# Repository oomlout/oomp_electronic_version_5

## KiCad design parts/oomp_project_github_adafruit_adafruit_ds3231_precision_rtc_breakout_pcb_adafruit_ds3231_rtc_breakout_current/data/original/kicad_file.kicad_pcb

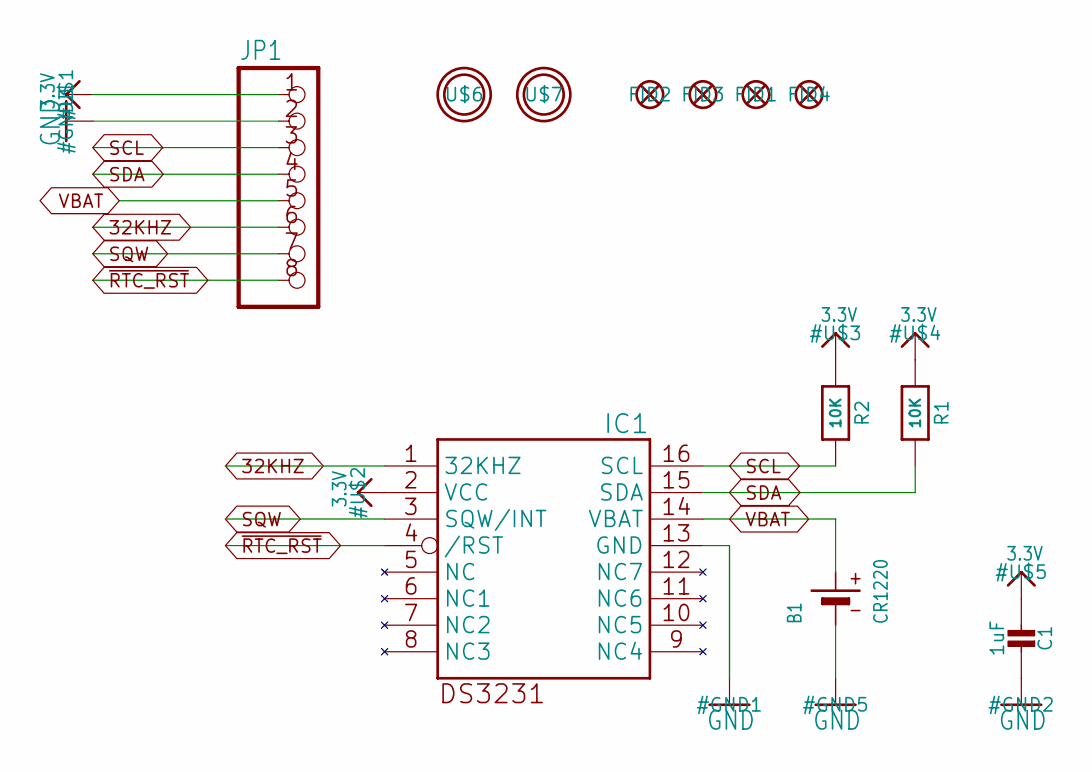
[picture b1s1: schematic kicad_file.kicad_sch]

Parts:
B1: CR1220
C1: 1uF; 0805-NO
FID1, FID2, FID3, FID4: FIDUCIAL""; FIDUCIAL_1MM
IC1: DS3231/SO; SO16W
JP1: HEADER-1X870MIL; 1X08_ROUND_70
R1, R2: 10K; 0805-NO
U$6, U$7: MOUNTINGHOLE2.5; MOUNTINGHOLE_2.5_PLATED

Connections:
3.3V: C1.2, IC1.2 (VCC), JP1.1, R1.1, R2.1
32KHZ: IC1.1 (32KHZ), JP1.6
GND: B1.-, C1.1, IC1.13 (GND), JP1.2
SCL: IC1.16 (SCL), JP1.3, R2.2
SDA: IC1.15 (SDA), JP1.4, R1.2
SQW: IC1.3 (SQW/INT), JP1.7
VBAT: B1.+$1 (+), IC1.14 (VBAT), JP1.5
~RTC_RST: IC1.4 (/RST), JP1.8

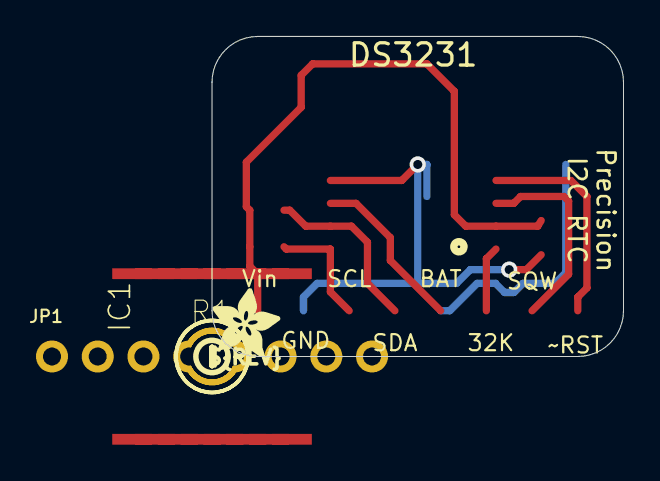
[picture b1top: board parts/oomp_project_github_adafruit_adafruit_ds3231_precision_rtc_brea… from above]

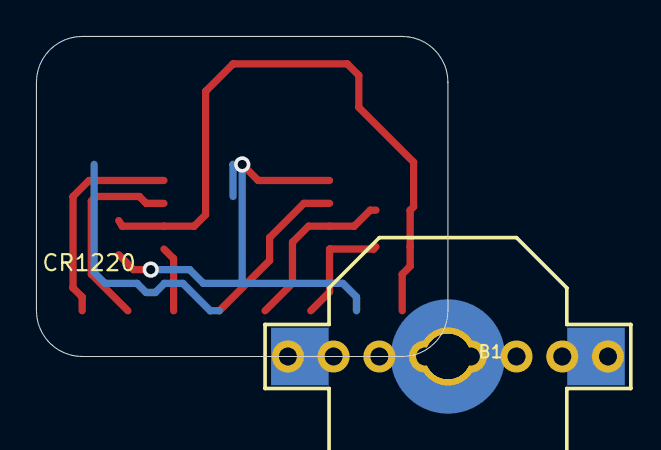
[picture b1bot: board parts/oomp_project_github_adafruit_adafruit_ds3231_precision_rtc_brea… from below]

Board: 16 copper layers, 22.9 x 17.8 mm, 14 parts (3 on the bottom side), 8 nets.

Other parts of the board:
U$8: ADAFRUIT_3.5MM
U$9: PCBFEAT-REV-040

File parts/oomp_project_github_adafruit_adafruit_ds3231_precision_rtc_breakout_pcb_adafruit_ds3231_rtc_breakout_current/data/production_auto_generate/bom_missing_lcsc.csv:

Designator,Comment,Footprint,OOMP ID,Reason
B1,CR1220,Adafruit DS3231 RTC Breakout-import-fps:CR1220,,No verified LCSC part number
C1,1uF,Adafruit DS3231 RTC Breakout-import-fps:0805-NO,,No verified LCSC part number
IC1,DS3231/SO,Adafruit DS3231 RTC Breakout-import-fps:SO16W,,No verified LCSC part number
U$8,,Adafruit DS3231 RTC Breakout-import-fps:ADAFRUIT_3.5MM,,No verified LCSC part number
U$9,,Adafruit DS3231 RTC Breakout-import-fps:PCBFEAT-REV-040,,No verified LCSC part number

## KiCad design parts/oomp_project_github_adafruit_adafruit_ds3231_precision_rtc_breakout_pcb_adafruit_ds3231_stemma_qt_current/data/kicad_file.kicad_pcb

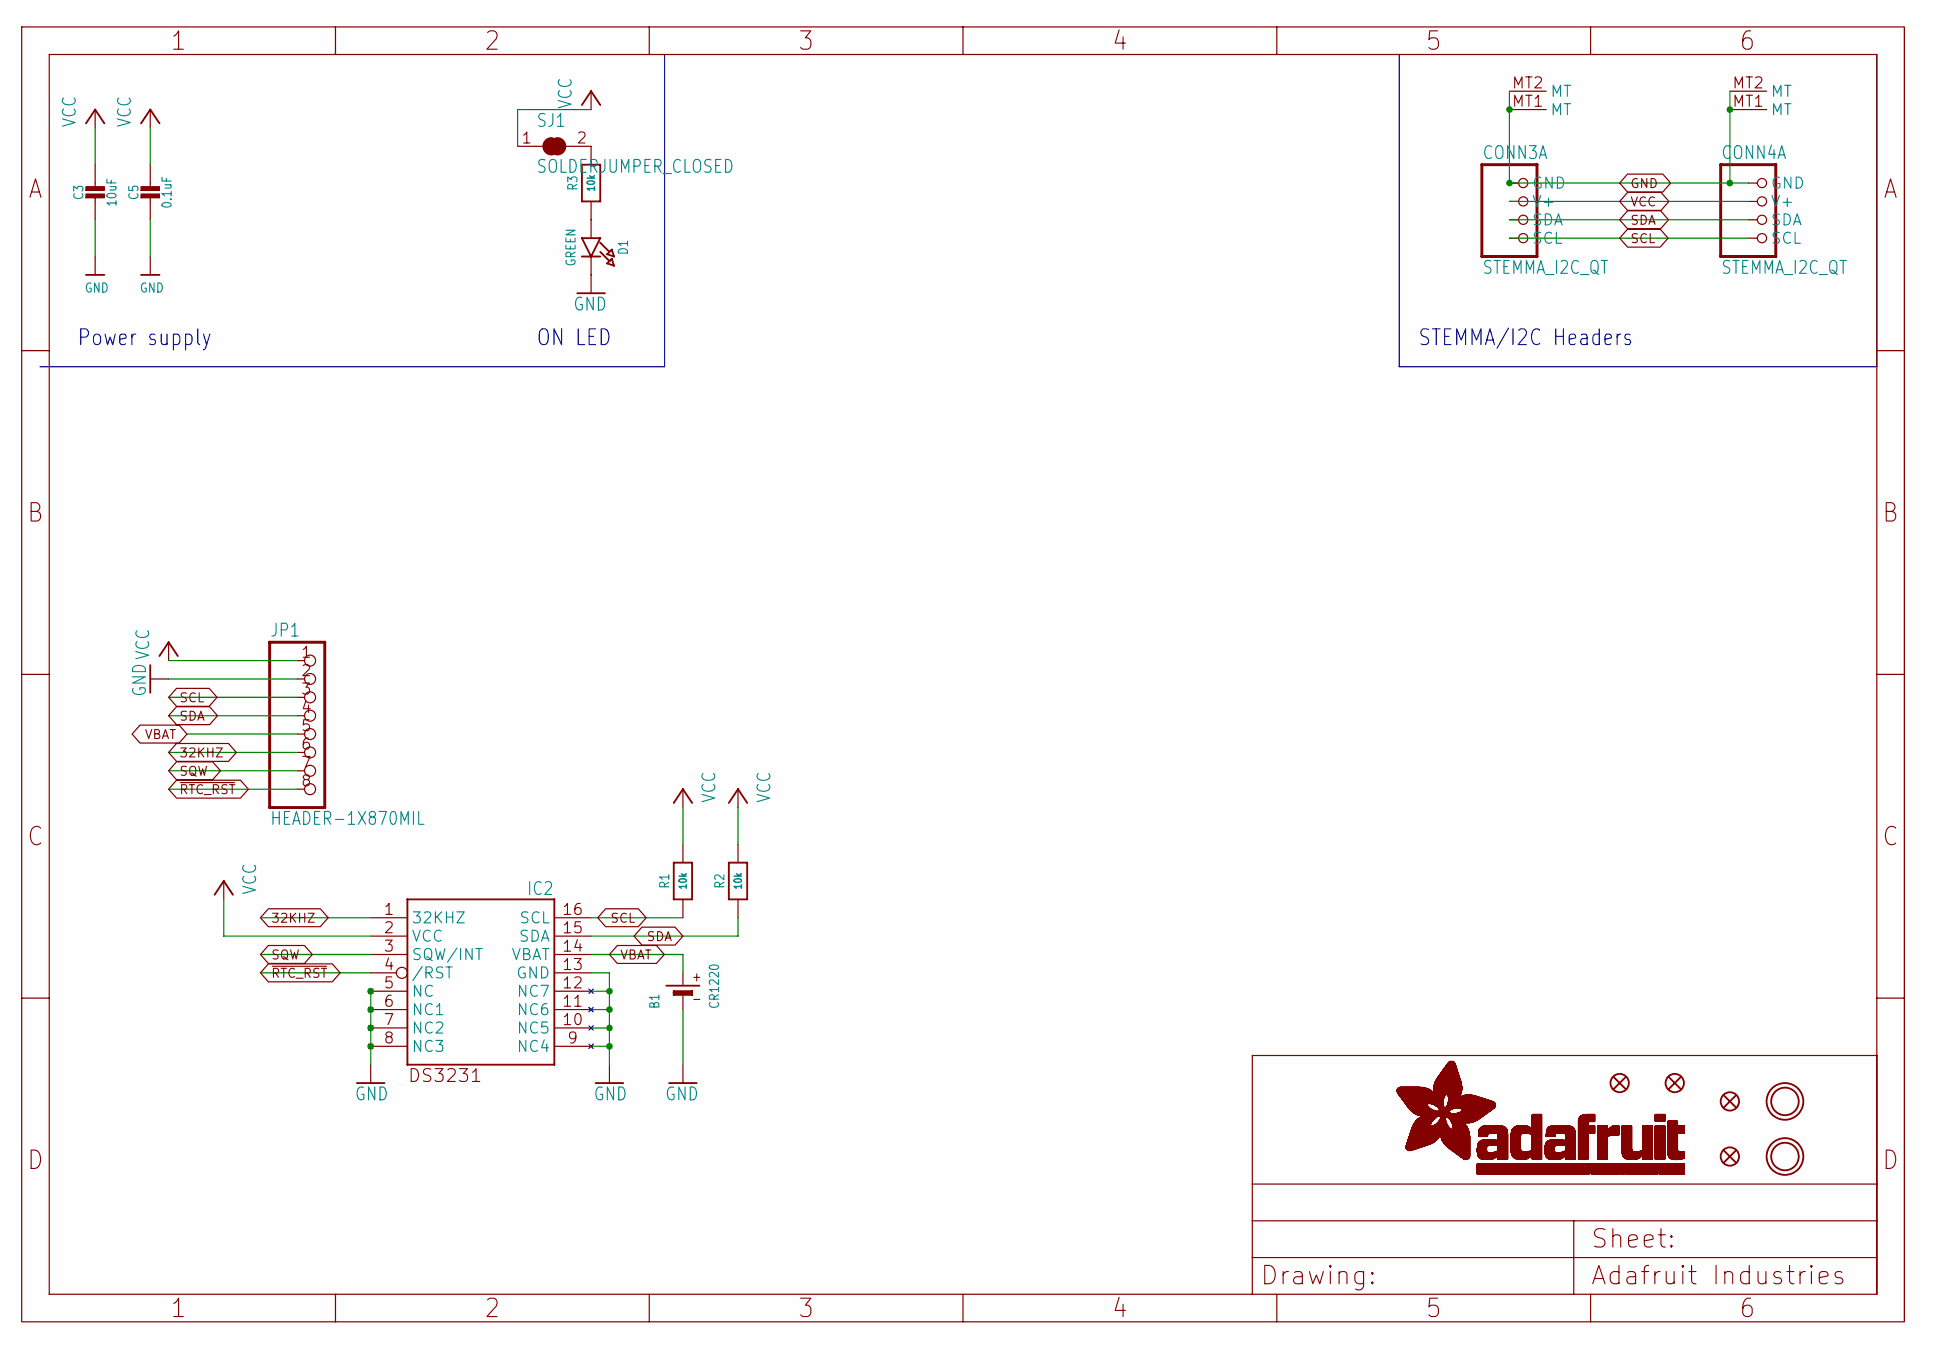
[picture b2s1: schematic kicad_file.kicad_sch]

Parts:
B1: CR1220
C3: 10uF; 0805-NO
C5: 0.1uF; 0603-NO
CONN3, CONN4: STEMMA_I2C_QT; JST_SH4
D1: GREEN; CHIPLED_0603_NOOUTLINE
FID1, FID2, FID3, FID4: FIDUCIAL_1MM
IC2: DS3231/SO; SO16W
JP1: HEADER-1X870MIL; 1X08_ROUND_70
R1, R2, R3: 10k; 0603-NO
SJ1: SOLDERJUMPER_CLOSED; SOLDERJUMPER_CLOSEDWIRE
U$9, U$17: MOUNTINGHOLE3.0THIN; MOUNTINGHOLE_3.0_PLATEDTHIN

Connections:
32KHZ: IC2.1 (32KHZ), JP1.6
GND: B1.-, C3.2, C5.2, CONN3.1 (GND), CONN3.MT1 (MT), CONN3.MT2 (MT), CONN4.1 (GND), CONN4.MT1 (MT), CONN4.MT2 (MT), D1.C, IC2.5 (NC), IC2.6 (NC1), IC2.7 (NC2), IC2.8 (NC3), IC2.9 (NC4), IC2.10 (NC5), IC2.11 (NC6), IC2.12 (NC7), IC2.13 (GND), JP1.2
unnamed: R3.2, SJ1.2
unnamed: D1.A, R3.1
SCL: CONN3.4 (SCL), CONN4.4 (SCL), IC2.16 (SCL), JP1.3, R1.1
SDA: CONN3.3 (SDA), CONN4.3 (SDA), IC2.15 (SDA), JP1.4, R2.1
SQW: IC2.3 (SQW/INT), JP1.7
VBAT: B1.+$1 (+), B1.+$2 (+), IC2.14 (VBAT), JP1.5
VCC: C3.1, C5.1, CONN3.2 (V+), CONN4.2 (V+), IC2.2 (VCC), JP1.1, R1.2, R2.2, SJ1.1
~RTC_RST: IC2.4 (/RST), JP1.8

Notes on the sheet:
Power supply
ON LED
STEMMA/I2C Headers

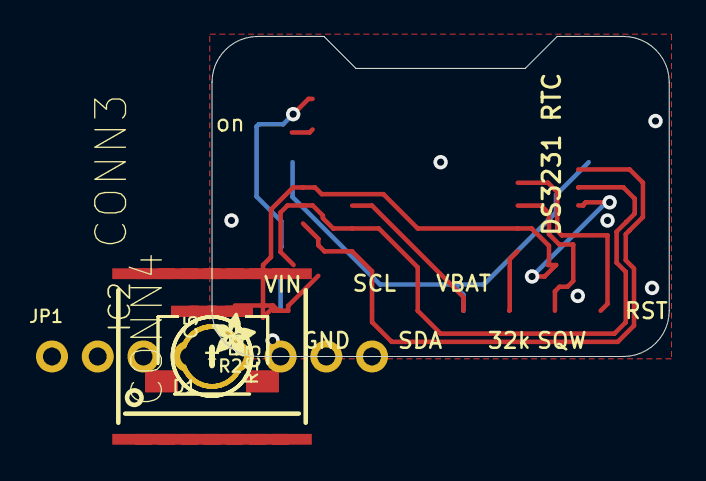
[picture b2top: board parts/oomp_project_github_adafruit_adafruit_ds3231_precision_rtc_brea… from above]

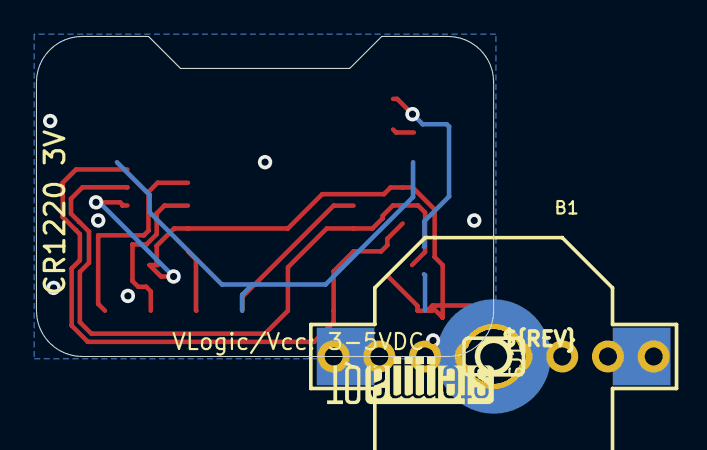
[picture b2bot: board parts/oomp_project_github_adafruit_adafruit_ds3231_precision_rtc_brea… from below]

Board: 16 copper layers, 25.4 x 17.8 mm, 21 parts (6 on the bottom side), 10 nets.

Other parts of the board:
U$1: ADAFRUIT_2.5MM
U$25: PCBFEAT-REV-040
U$31: STEMMAQT

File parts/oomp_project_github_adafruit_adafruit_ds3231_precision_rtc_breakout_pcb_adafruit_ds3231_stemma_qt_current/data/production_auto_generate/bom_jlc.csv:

Comment,Designator,Footprint,LCSC Part #
,JP1,Adafruit DS3231 STEMMA QT-import-fps:1X08_ROUND_70,C492421
,U$1,Adafruit DS3231 STEMMA QT-import-fps:ADAFRUIT_2.5MM,
,U$25,Adafruit DS3231 STEMMA QT-import-fps:PCBFEAT-REV-040,
,U$31,Adafruit DS3231 STEMMA QT-import-fps:STEMMAQT,
0.1uF,C5,Adafruit DS3231 STEMMA QT-import-fps:0603-NO,C14663
10k,"R1,R2,R3",Adafruit DS3231 STEMMA QT-import-fps:0603-NO,C98220
10uF,C3,Adafruit DS3231 STEMMA QT-import-fps:0805-NO,
CR1220,B1,Adafruit DS3231 STEMMA QT-import-fps:CR1220,
DS3231/SO,IC2,Adafruit DS3231 STEMMA QT-import-fps:SO16W,
GREEN,D1,Adafruit DS3231 STEMMA QT-import-fps:CHIPLED_0603_NOOUTLINE,
STEMMA_I2C_QT,"CONN3,CONN4",Adafruit DS3231 STEMMA QT-import-fps:JST_SH4,C160404

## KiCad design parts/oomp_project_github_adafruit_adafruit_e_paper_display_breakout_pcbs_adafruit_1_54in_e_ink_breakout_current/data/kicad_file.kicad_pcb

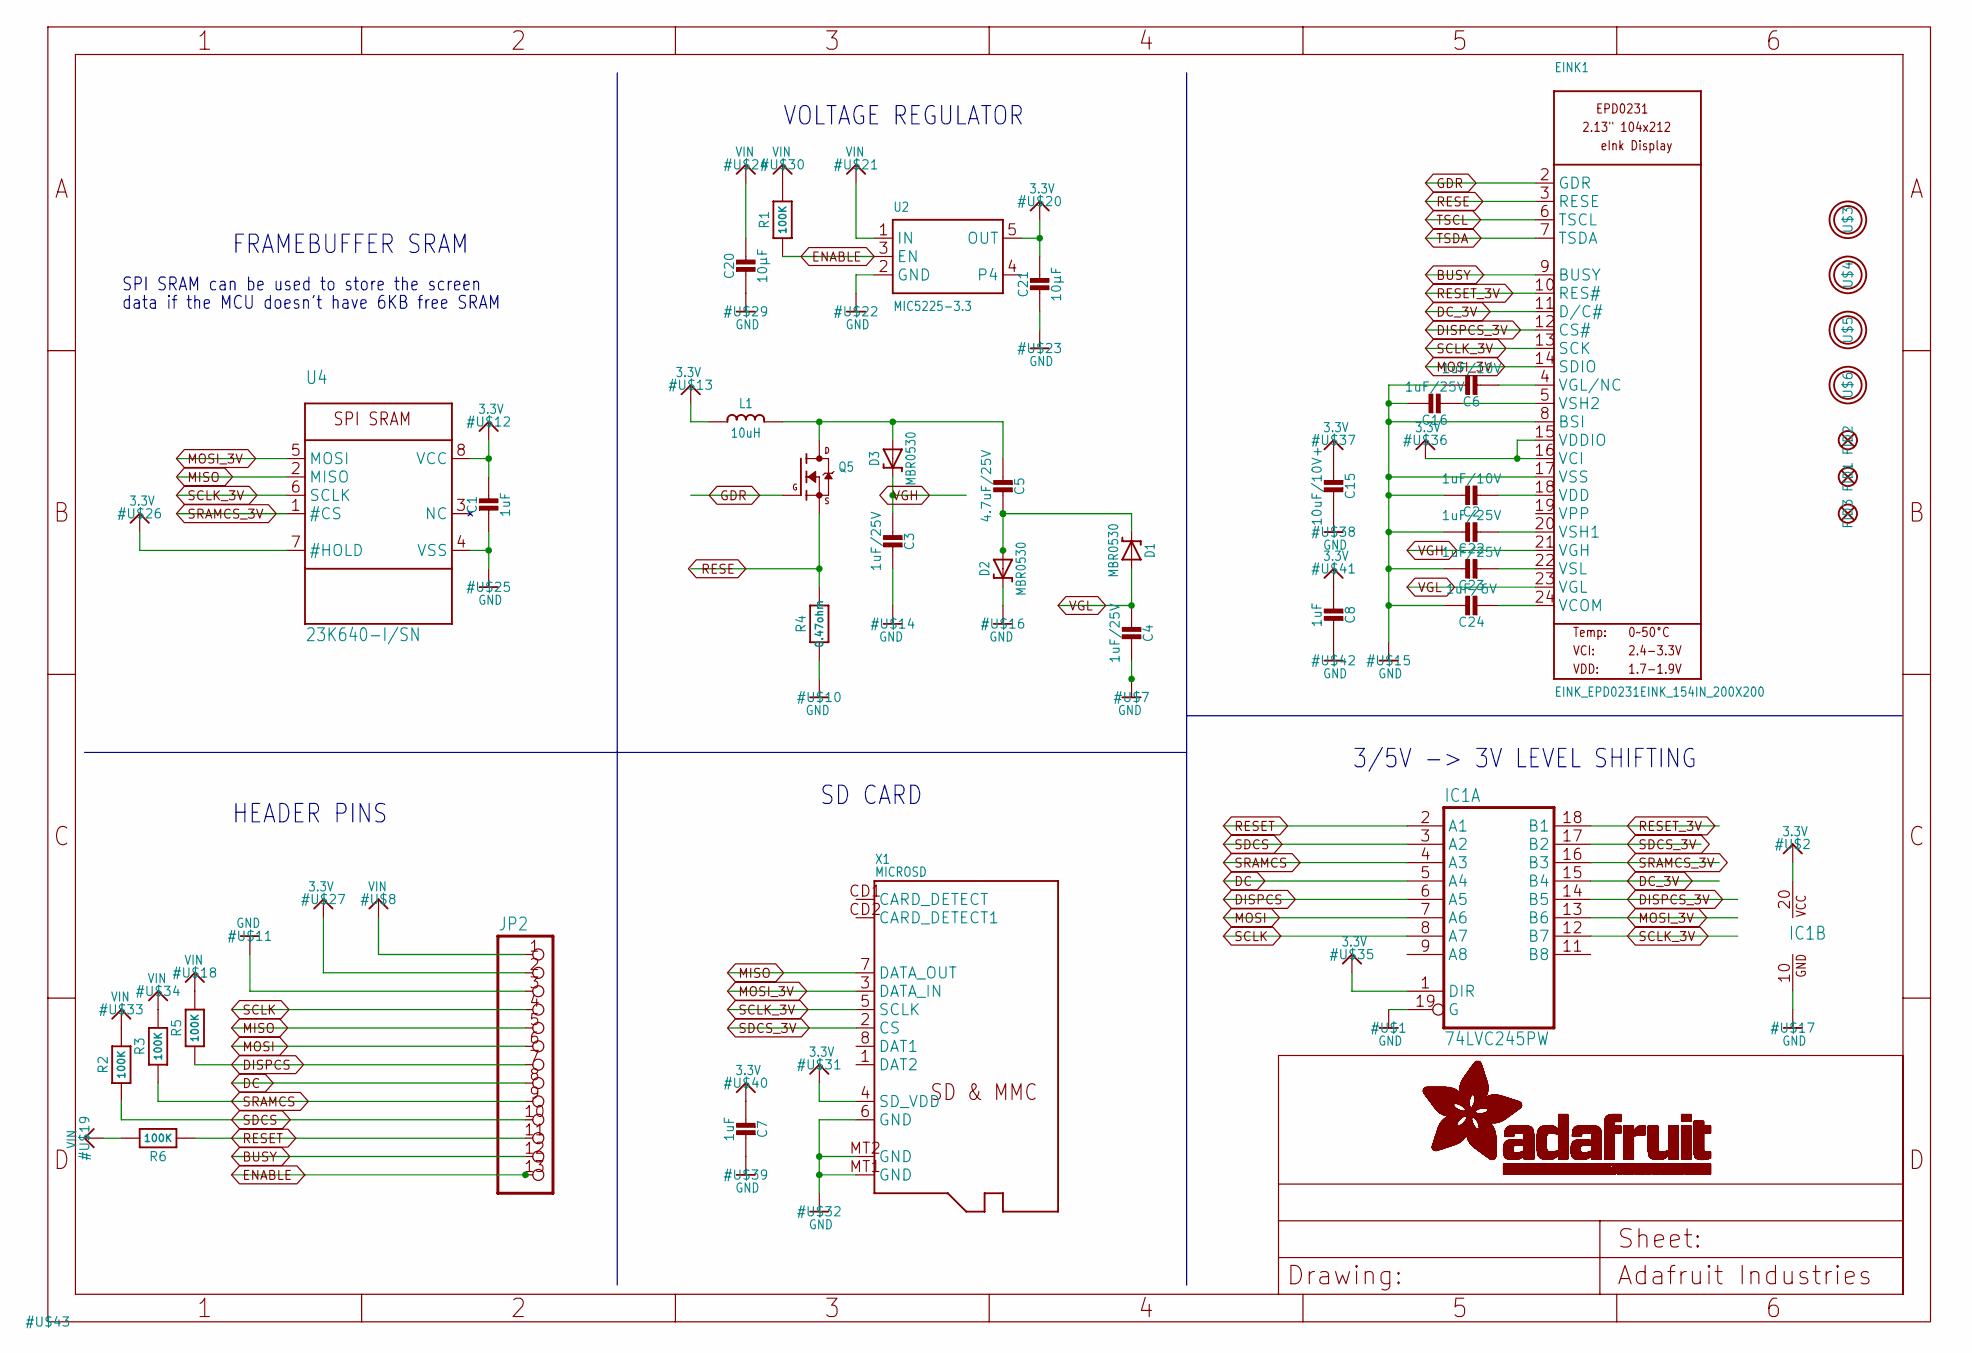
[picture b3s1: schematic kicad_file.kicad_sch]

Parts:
C1: 1uF; 0805_10MGAP
C2, C6: 1uF/10V; 0805-NO
C3, C4, C16, C22, C23: 1uF/25V; 0805-NO
C5: 4.7uF/25V; 0805-NO
C7, C8: 1uF; 0805-NO
C15: 10uF/10V+; 0805-NO
C20, C21: 10µF; 0805-NO
C24: 1uF/6V; 0805-NO
D1, D2, D3: MBR0530; SOD-123
EINK1: EINK_EPD0231EINK_154IN_200X200; EINK_154IN
FID1, FID2, FID3: FIDUCIAL_1MM
IC1: 74LVC245PW; TSSOP20
JP2: HEADER-1X13; 1X13_ROUND_70
L1: 10uH; INDUCTOR_4X4MM_NR401
Q5: IRLML0100; SOT23-3
R1, R2, R3, R5, R6: 100K; 0805-NO
R4: 0.47ohm; 0805_10MGAP
U2: MIC5225-3.3; SOT23-5
U4: 23K640-I/SN; SOIC8_150MIL
U$3, U$4, U$5, U$6: MOUNTINGHOLE2.5; MOUNTINGHOLE_2.5_PLATED
X1: MICROSD

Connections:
3.3V: C1.1, C7.1, C8.1, C15.2, C21.1, EINK1.15 (VDDIO), EINK1.16 (VCI), IC1.1 (DIR), IC1.20 (VCC), JP2.2, L1.P$2 (2), U2.5 (OUT), U4.7 (#HOLD), U4.8 (VCC), X1.4 (SD_VDD)
BUSY: EINK1.9 (BUSY), JP2.12
DC: IC1.5 (A4), JP2.8
DC_3V: EINK1.11 (D/C#), IC1.15 (B4)
DISPCS: IC1.6 (A5), JP2.7, R5.1
DISPCS_3V: EINK1.12 (CS#), IC1.14 (B5)
ENABLE: JP2.13, R1.1, U2.3 (EN)
GDR: EINK1.2 (GDR), Q5.1 (G)
GND: C1.2, C2.1, C3.2, C4.2, C6.1, C7.2, C8.2, C15.1, C16.1, C20.2, C21.2, C22.1, C23.1, C24.1, D2.C, EINK1.8 (BSI), EINK1.17 (VSS), IC1.10 (GND), IC1.19 (G), JP2.3, R4.2, U2.2 (GND), U4.4 (VSS), X1.6 (GND), X1.MT1 (GND), X1.MT2 (GND)
MISO: JP2.5, U4.2 (MISO), X1.7 (DATA_OUT)
MOSI: IC1.7 (A6), JP2.6
MOSI_3V: EINK1.14 (SDIO), IC1.13 (B6), U4.5 (MOSI), X1.3 (DATA_IN)
unnamed: C5.2, D1.C, D2.A
unnamed: C5.1, D3.A, L1.P$1 (1), Q5.3 (D)
unnamed: C16.2, EINK1.5 (VSH2)
unnamed: C2.2, EINK1.18 (VDD)
unnamed: C22.2, EINK1.20 (VSH1)
unnamed: C6.2, EINK1.4 (VGL/NC)
unnamed: C23.2, EINK1.22 (VSL)
unnamed: C24.2, EINK1.24 (VCOM)
RESE: EINK1.3 (RESE), Q5.2 (S), R4.1
RESET: IC1.2 (A1), JP2.11, R6.1
RESET_3V: EINK1.10 (RES#), IC1.18 (B1)
SCLK: IC1.8 (A7), JP2.4
SCLK_3V: EINK1.13 (SCK), IC1.12 (B7), U4.6 (SCLK), X1.5 (SCLK)
SDCS: IC1.3 (A2), JP2.10, R2.1
SDCS_3V: IC1.17 (B2), X1.2 (CS)
SRAMCS: IC1.4 (A3), JP2.9, R3.1
SRAMCS_3V: IC1.16 (B3), U4.1 (#CS)
TSCL: EINK1.6 (TSCL)
TSDA: EINK1.7 (TSDA)
VGH: C3.1, D3.C, EINK1.21 (VGH)
VGL: C4.1, D1.A, EINK1.23 (VGL)
VIN: C20.1, JP2.1, R1.2, R2.2, R3.2, R5.2, R6.2, U2.1 (IN)

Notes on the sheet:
SD CARD
FRAMEBUFFER SRAM
3/5V -> 3V LEVEL SHIFTING
VOLTAGE REGULATOR
HEADER PINS
SPI SRAM can be used to store the screen
data if the MCU doesn't have 6KB free SRAM

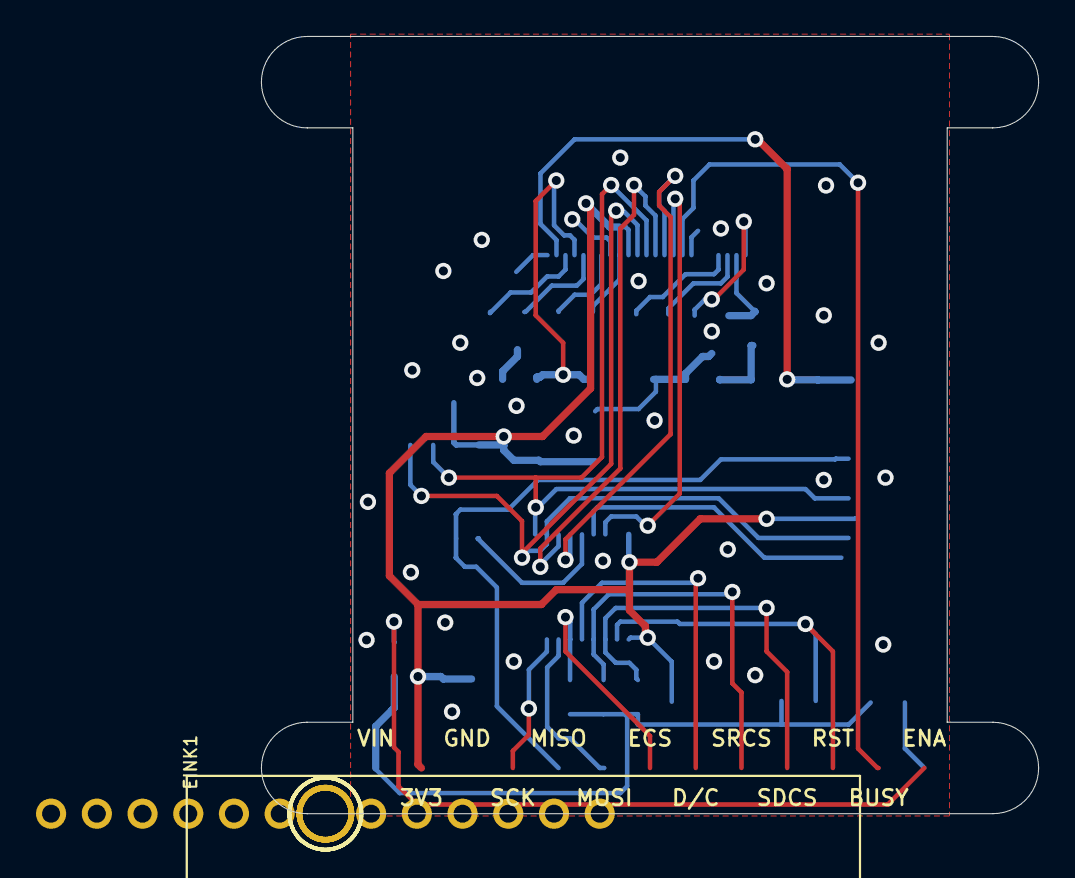
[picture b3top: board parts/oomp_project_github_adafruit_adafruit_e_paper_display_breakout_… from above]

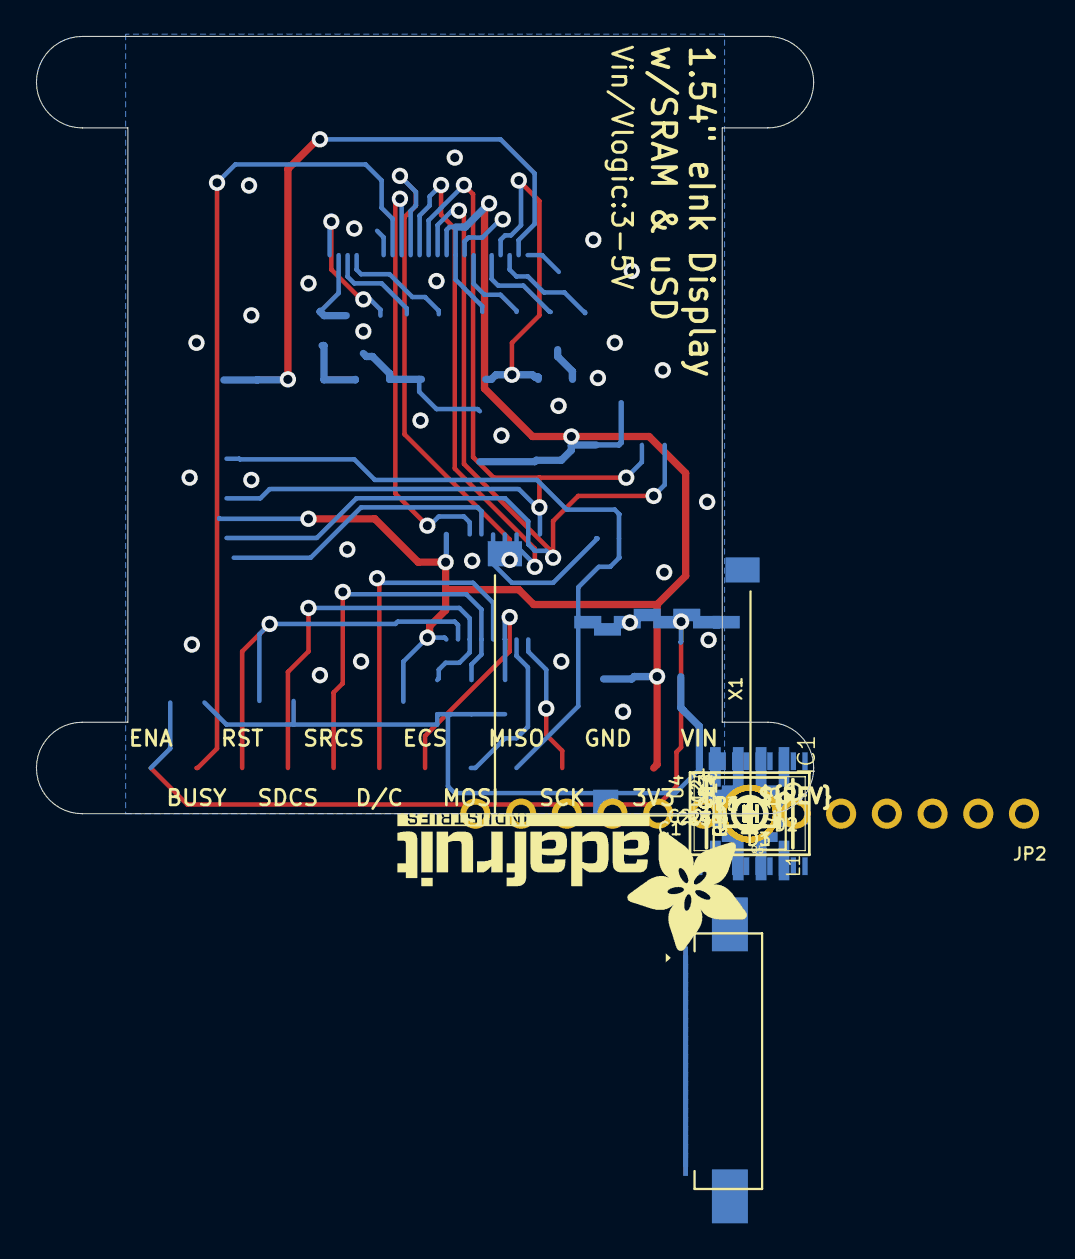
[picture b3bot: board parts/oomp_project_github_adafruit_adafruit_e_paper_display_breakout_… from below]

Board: 2 copper layers, 43.2 x 43.2 mm, 41 parts (36 on the bottom side), 32 nets.

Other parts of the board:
U$9: PCBFEAT-REV-040
U$28: ADAFRUIT_TEXT_20MM

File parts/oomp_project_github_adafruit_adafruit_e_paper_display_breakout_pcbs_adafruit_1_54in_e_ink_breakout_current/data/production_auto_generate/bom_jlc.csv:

Comment,Designator,Footprint,LCSC Part #
,JP2,Adafruit 1.54in eInk Breakout-import-fps:1X13_ROUND_70,C2894936
,U$28,Adafruit 1.54in eInk Breakout-import-fps:ADAFRUIT_TEXT_20MM,
,U$9,Adafruit 1.54in eInk Breakout-import-fps:PCBFEAT-REV-040,
0.47ohm,R4,Adafruit 1.54in eInk Breakout-import-fps:0805_10MGAP,
100K,"R1,R2,R3,R5,R6",Adafruit 1.54in eInk Breakout-import-fps:0805-NO,C149504
10uF/10V+,C15,Adafruit 1.54in eInk Breakout-import-fps:0805-NO,
10uH,L1,Adafruit 1.54in eInk Breakout-import-fps:INDUCTOR_4X4MM_NR401,
10µF,"C20,C21",Adafruit 1.54in eInk Breakout-import-fps:0805-NO,
1uF,"C7,C8",Adafruit 1.54in eInk Breakout-import-fps:0805-NO,
1uF,C1,Adafruit 1.54in eInk Breakout-import-fps:0805_10MGAP,
1uF/10V,"C2,C6",Adafruit 1.54in eInk Breakout-import-fps:0805-NO,
1uF/25V,"C3,C4,C16,C22,C23",Adafruit 1.54in eInk Breakout-import-fps:0805-NO,
1uF/6V,C24,Adafruit 1.54in eInk Breakout-import-fps:0805-NO,
23K640-I/SN,U4,Adafruit 1.54in eInk Breakout-import-fps:SOIC8_150MIL,
4.7uF/25V,C5,Adafruit 1.54in eInk Breakout-import-fps:0805-NO,
74LVC245PW,IC1,Adafruit 1.54in eInk Breakout-import-fps:TSSOP20,
EINK_EPD0231EINK_154IN_200X200,EINK1,Adafruit 1.54in eInk Breakout-import-fps:EINK_154IN,
IRLML0100,Q5,Adafruit 1.54in eInk Breakout-import-fps:SOT23-3,
MBR0530,"D1,D2,D3",Adafruit 1.54in eInk Breakout-import-fps:SOD-123,
MIC5225-3.3,U2,Adafruit 1.54in eInk Breakout-import-fps:SOT23-5,
MICROSD,X1,Adafruit 1.54in eInk Breakout-import-fps:MICROSD,

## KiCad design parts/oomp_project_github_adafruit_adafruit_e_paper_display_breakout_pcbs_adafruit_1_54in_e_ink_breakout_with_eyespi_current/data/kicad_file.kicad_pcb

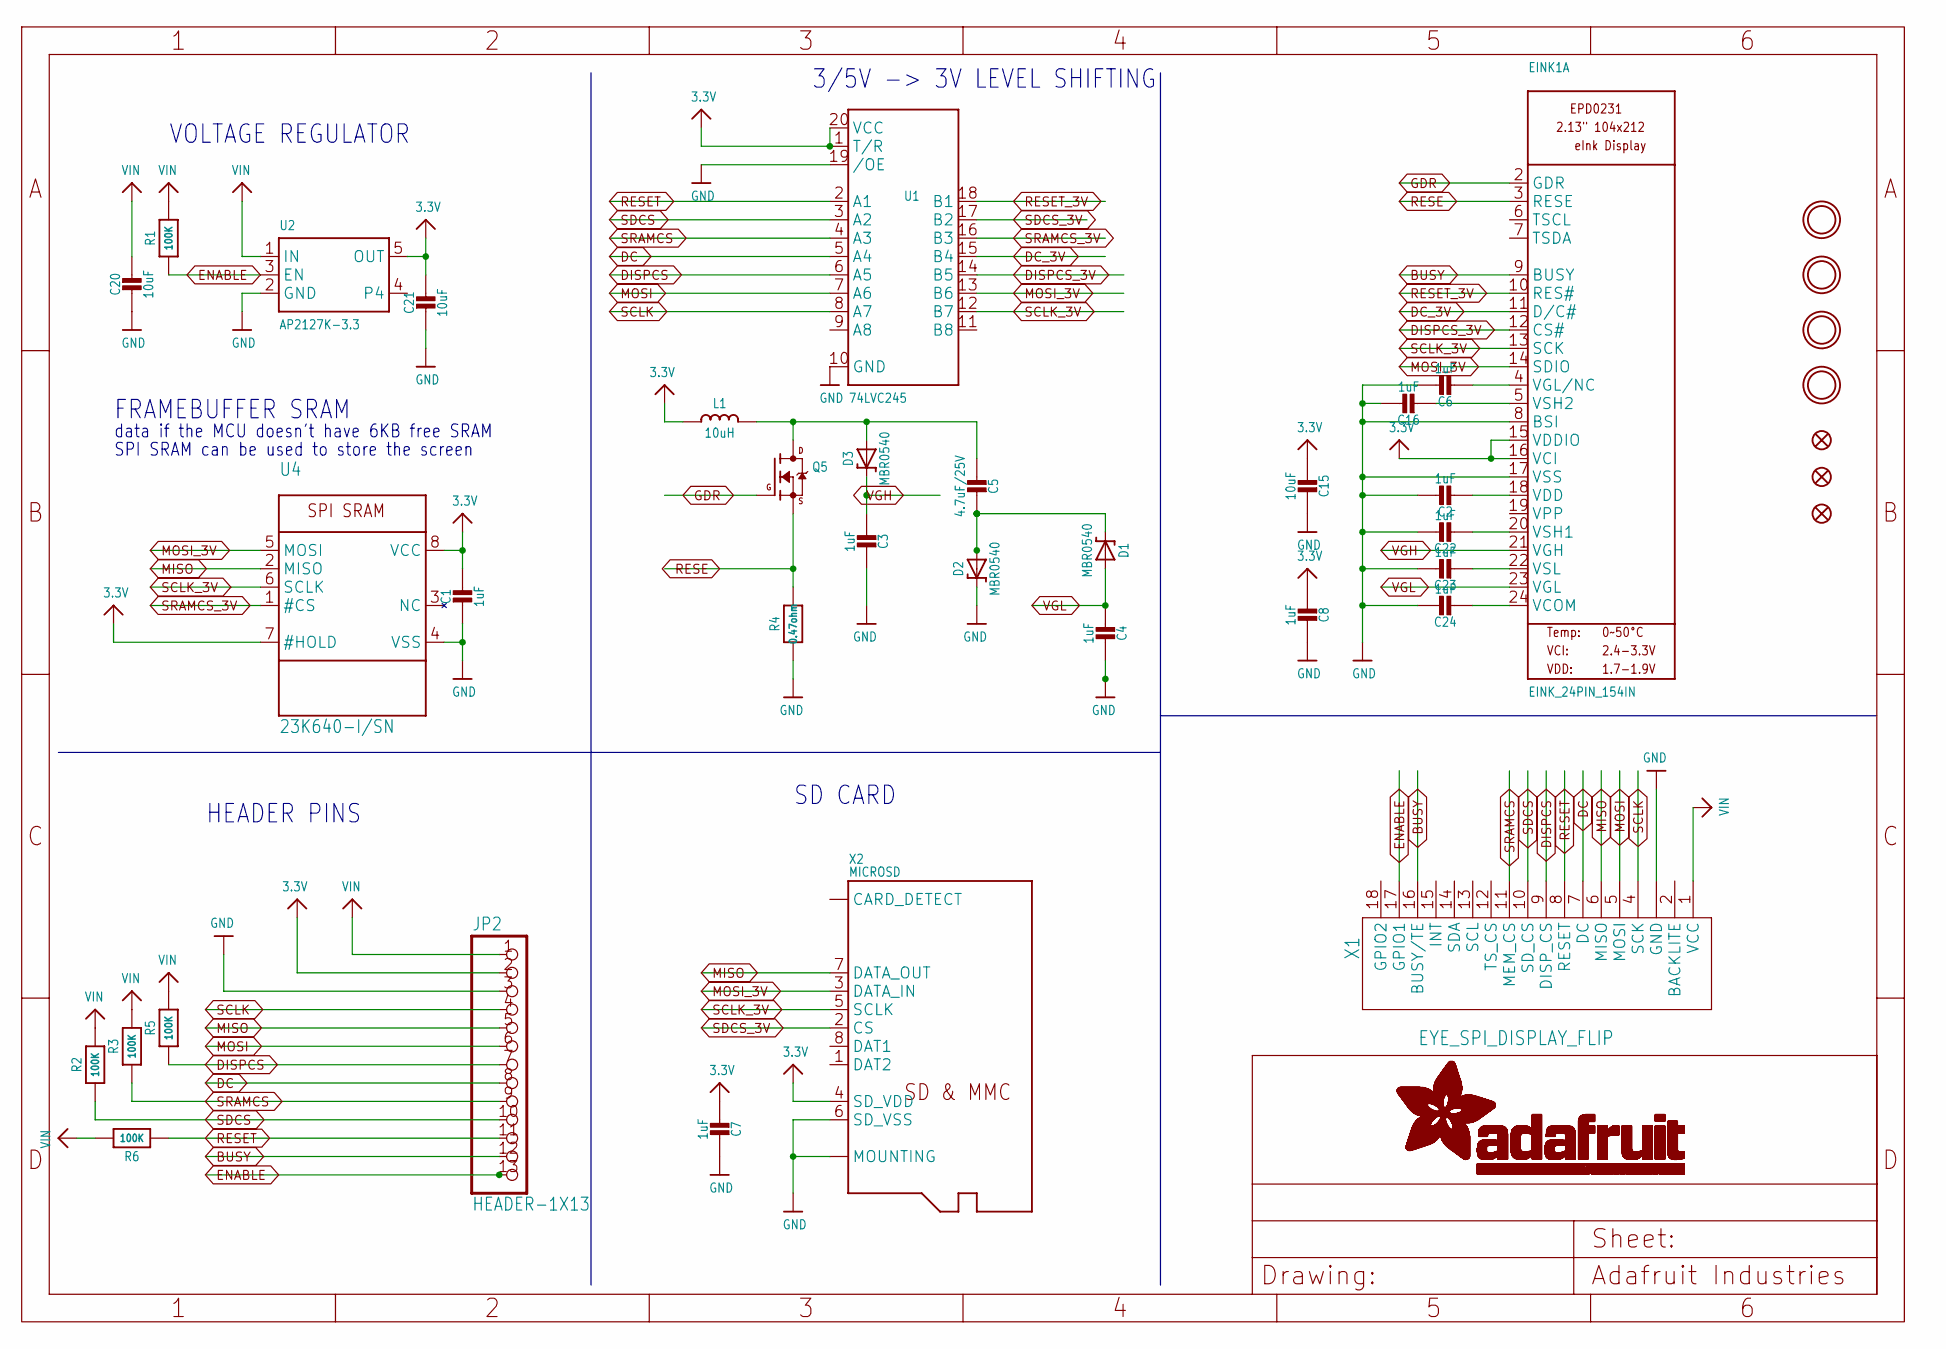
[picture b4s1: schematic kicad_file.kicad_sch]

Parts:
C1, C2, C3, C4, C6, C7, C8, C16, C22, C23, C24: 1uF; 0805-NO
C5: 4.7uF/25V; 0805-NO
C15, C20, C21: 10uF; 0805-NO
D1, D2, D3: MBR0540; SOD-123
EINK1: EINK_24PIN_154IN; EINK_154IN
FID1, FID2, FID3: FIDUCIAL_1MM
JP2: HEADER-1X13; 1X13_ROUND_70
L1: 10uH; INDUCTOR_4X4MM_NR401
Q5: IRLML0100; SOT23-3
R1, R2, R3, R5, R6: 100K; 0805-NO
R4: 0.47ohm; 0805_10MGAP
U1: 74LVC245; TSSOP20
U2: AP2127K-3.3; SOT23-5; JLC_ROTATION 270
U4: 23K640-I/SN; SOIC8_150MIL
U$3, U$4, U$5, U$6: MOUNTINGHOLE2.5; MOUNTINGHOLE_2.5_PLATED
X1: EYE_SPI_DISPLAY_FLIP; EYE_SPI_DISPLAY_BOTCONTACT; LCSC C2856802
X2: MICROSD; JLC_ROTATION 90

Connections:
3.3V: C1.1, C7.1, C8.1, C15.2, C21.1, EINK1.15 (VDDIO), EINK1.16 (VCI), JP2.2, L1.P$2 (2), U1.1 (T/R), U1.20 (VCC), U2.5 (OUT), U4.7 (#HOLD), U4.8 (VCC), X2.4 (SD_VDD)
BUSY: EINK1.9 (BUSY), JP2.12, X1.16 (BUSY/TE)
DC: JP2.8, U1.5 (A4), X1.7 (DC)
DC_3V: EINK1.11 (D/C#), U1.15 (B4)
DISPCS: JP2.7, R5.1, U1.6 (A5), X1.9 (DISP_CS)
DISPCS_3V: EINK1.12 (CS#), U1.14 (B5)
ENABLE: JP2.13, R1.1, U2.3 (EN), X1.17 (GPIO1)
GDR: EINK1.2 (GDR), Q5.1 (G)
GND: C1.2, C2.1, C3.2, C4.2, C6.1, C7.2, C8.2, C15.1, C16.1, C20.2, C21.2, C22.1, C23.1, C24.1, D2.C, EINK1.8 (BSI), EINK1.17 (VSS), JP2.3, R4.2, U1.10 (GND), U1.19 (/OE), U2.2 (GND), U4.4 (VSS), X1.3 (GND), X1.SUPPORT1 (GND), X1.SUPPORT2 (GND), X2.6 (SD_VSS), X2.MT1 (MOUNTING), X2.MT2 (MOUNTING)
MISO: JP2.5, U4.2 (MISO), X1.6 (MISO), X2.7 (DATA_OUT)
MOSI: JP2.6, U1.7 (A6), X1.5 (MOSI)
MOSI_3V: EINK1.14 (SDIO), U1.13 (B6), U4.5 (MOSI), X2.3 (DATA_IN)
unnamed: C5.2, D1.C, D2.A
unnamed: C5.1, D3.A, L1.P$1 (1), Q5.3 (D)
unnamed: C16.2, EINK1.5 (VSH2)
unnamed: C2.2, EINK1.18 (VDD)
unnamed: C22.2, EINK1.20 (VSH1)
unnamed: C6.2, EINK1.4 (VGL/NC)
unnamed: C23.2, EINK1.22 (VSL)
unnamed: C24.2, EINK1.24 (VCOM)
RESE: EINK1.3 (RESE), Q5.2 (S), R4.1
RESET: JP2.11, R6.1, U1.2 (A1), X1.8 (RESET)
RESET_3V: EINK1.10 (RES#), U1.18 (B1)
SCLK: JP2.4, U1.8 (A7), X1.4 (SCK)
SCLK_3V: EINK1.13 (SCK), U1.12 (B7), U4.6 (SCLK), X2.5 (SCLK)
SDCS: JP2.10, R2.1, U1.3 (A2), X1.10 (SD_CS)
SDCS_3V: U1.17 (B2), X2.2 (CS)
SRAMCS: JP2.9, R3.1, U1.4 (A3), X1.11 (MEM_CS)
SRAMCS_3V: U1.16 (B3), U4.1 (#CS)
VGH: C3.1, D3.C, EINK1.21 (VGH)
VGL: C4.1, D1.A, EINK1.23 (VGL)
VIN: C20.1, JP2.1, R1.2, R2.2, R3.2, R5.2, R6.2, U2.1 (IN), X1.1 (VCC)

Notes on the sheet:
3/5V -> 3V LEVEL SHIFTING
HEADER PINS
SPI SRAM can be used to store the screen
SD CARD
FRAMEBUFFER SRAM
data if the MCU doesn't have 6KB free SRAM
VOLTAGE REGULATOR
